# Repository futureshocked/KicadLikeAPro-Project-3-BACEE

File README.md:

# KicadLikeAPro-Project-3-BACEE

This is one of the PCB projects from the [Kicad Like a Pro](https://techexplorations.com/so/kicada/) book and video course. It contains a two and four layer board that implements an Arduino clone with external EEPROM and a clock.

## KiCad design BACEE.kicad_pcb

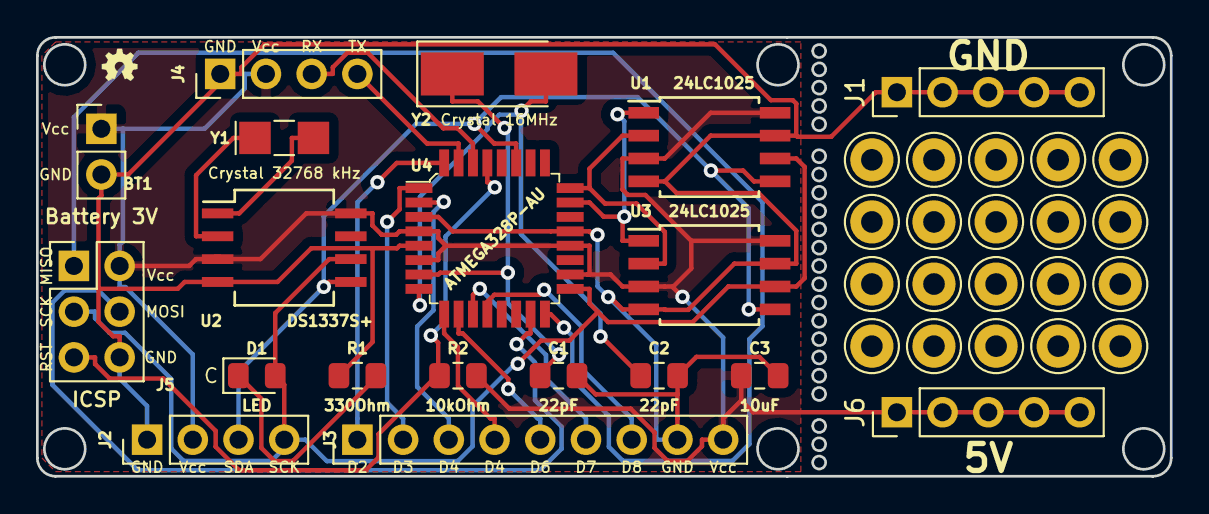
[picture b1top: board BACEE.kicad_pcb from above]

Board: 2 copper layers, 63.0 x 24.4 mm, 40 parts (0 on the bottom side), 23 nets.

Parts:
BT1: Battery 3V; PinHeader_1x02_P2.54mm_Vertical
C1, C2: 22pF; C_0805_2012Metric_Pad1.15x1.40mm_HandSolder
C3: 10uF; C_0805_2012Metric_Pad1.15x1.40mm_HandSolder
D1: LED; LED_0805_2012Metric_Pad1.15x1.40mm_HandSolder
J1: GND_rail; PinHeader_1x05_P2.54mm_Vertical
J2: I2C connector; PinHeader_1x04_P2.54mm_Vertical
J3: Digital pins; PinHeader_1x09_P2.54mm_Vertical
J4: Serial connector; PinHeader_1x04_P2.54mm_Vertical
J5: ICSP; PinHeader_2x03_P2.54mm_Vertical
J6: 5V_Rail; PinHeader_1x05_P2.54mm_Vertical
J7, J8, J9, J10, J11, J12, J13, J14, J15, J16, J17, J18, J19, J20, J21, J22, J23, J24, J25, J26: Conn_01x01_Female; Pin_D1.0mm_L10.0mm_LooseFit
LOGO_OSHW_silkscreen_2mm: val**; LOGO_OSHW_silkscreen_2mm
R1: 330Ohm; R_0805_2012Metric_Pad1.15x1.40mm_HandSolder
R2: 10kOhm; R_0805_2012Metric_Pad1.15x1.40mm_HandSolder
U1, U3: 24LC1025; SOIJ-8_5.3x5.3mm_P1.27mm
U2: DS1337S+; SO-8_5.3x6.2mm_P1.27mm
U4: ATMEGA328P-AU; TQFP-32_7x7mm
Y1: Crystal 32768 kHz; Crystal_SMD_MicroCrystal_CC7V-T1A-2Pin_3.2x1.5mm_HandSolder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
Y2: Crystal 16MHz; Crystal_SMD_5032-2Pin_5.0x3.2mm_HandSoldering

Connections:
/ADDS1: U1.1, U3.1, U4.23
/ADDS2: U1.2, U3.2, U4.24
/D2: J3.1, U4.32
/D3: J3.2, U4.1
/D4: J3.3, U4.2
/D5: J3.4, U4.9
/D6: J3.5, U4.10
/D7: J3.6, U4.11
/D8: J3.7, U4.12
/MISO: J5.1, U4.16
/MOSI: J5.4, U4.15
/RESET: J5.5, R2.1, U4.29
/RX: J4.3, U4.30
/SCK: D1.2, J2.4, J5.3, U1.6, U2.6, U3.6, U4.17
/SDA: J2.3, U1.5, U2.5, U3.5, U4.27
/TX: J4.4, U4.31
/Vcc: BT1.1, C3.1, J2.2, J3.9, J4.2, J5.2, J6.1, J6.2, J6.3, J6.4, J6.5, R2.2, U1.3, U1.8, U2.3, U2.8, U3.3, U3.8, U4.4, U4.6, U4.18, U4.20
GND: BT1.2, C1.2, C2.2, C3.2, J1.1, J1.2, J1.3, J1.4, J1.5, J2.1, J3.8, J4.1, J5.6, R1.1, U1.4, U1.7, U2.4, U3.4, U3.7, U4.3, U4.5, U4.21
unnamed: C1.1, U4.7, Y2.1
unnamed: C2.1, U4.8, Y2.2
unnamed: D1.1, R1.2
unnamed: U2.1, Y1.2
unnamed: U2.2, Y1.1

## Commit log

2018-08-21 First commit to new project.
2018-08-21 Added symbols to root sheet.
2018-08-21 Created Connectors sheet.
2018-08-21 Created I2C connector in Connectors sheet.
2018-08-21 Placed symbols in connectors sheet.
2018-08-21 Symbols placed.
2018-08-21 Annotated and edited symbol values.
2018-08-21 Labeled the ICSP connector.
2018-08-21 Wired MCU.
2018-08-22 Wired main symbols.
2018-08-22 Labeled sheet rectangle.
2018-08-22 Various corrections.
2018-08-22 Added informational graphics.
2018-08-22 Created netlist.
2018-08-23 Started layout work. Imported netlist and setup the sheet.
2018-08-23 Placement completed.
2018-08-23 Completed placement. Did a test run on FreeRouting.
2018-08-23 Completed placement and outline.
2018-08-23 Autorouted 2-layer version.
2018-08-23 Autorouted 4-layer version.
2018-08-23 Added GND copper fill.
2018-08-23 Completed silkscreen.
2018-08-23 Added distances.
2018-08-23 Added gerber files for the two-layer board.
2018-08-29 Created schematic for prototyping area.
2018-08-29 Added associations for new symbols.
2018-08-29 Created new netlist file.
2018-08-29 Completed design of extended board.
2018-09-17 Adjusted designators, units etc as per Larry's feedback.
2018-09-20 Enabled all layers in Pcbnew.
2018-09-20 Corrected a value, added 3D renders.
2019-02-18 Corrected addres pins of EEPROM modules.
2019-02-18 Corrected error in addressing pins of EEPROM modules.
2019-02-18 Fixed layout wiring to implement the fix in EEPROM addressing.
2019-02-18 Gerbers for version 1.1.
2019-02-18 Corrected EEPROM addressing error in the four layer board.
2019-02-18 Added copper zones.
2019-02-18 Fixed error in EEPROM addressing pins.
2020-11-05 Small fixes.
